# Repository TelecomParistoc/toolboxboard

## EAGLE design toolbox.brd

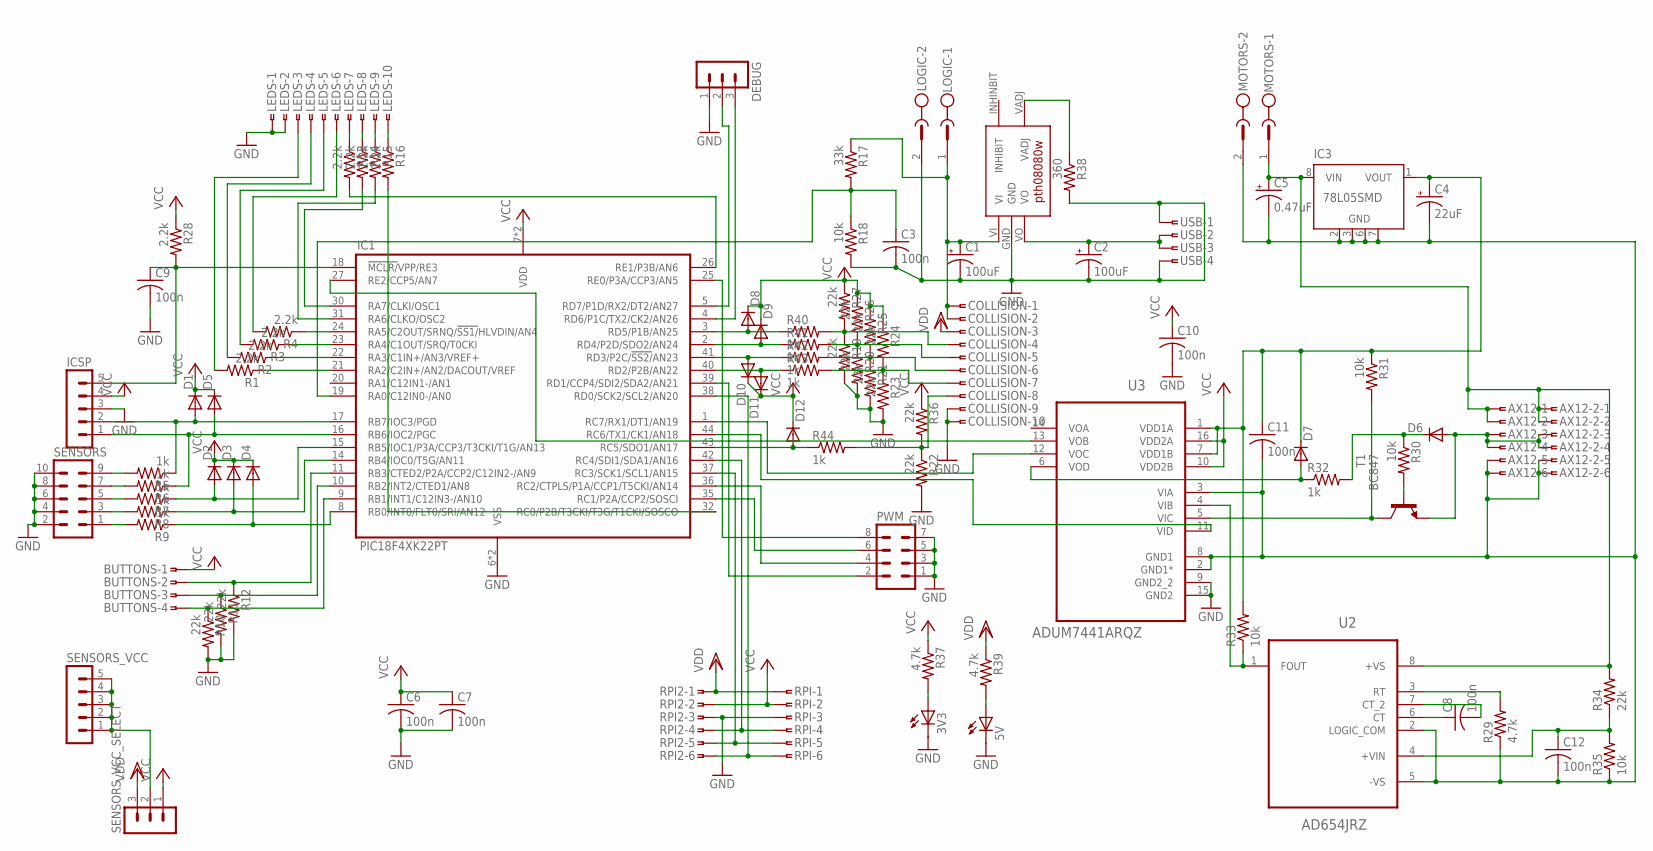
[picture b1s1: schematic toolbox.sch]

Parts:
3V3, 5V: LEDCHIPLED_0805; CHIPLED_0805
AX12, AX12-2: SMDTOP-6; SMDTOP6
BUTTONS: SMDTOP-4; SMDTOP4
C1, C2: 100uF; E2,5-6E
C3, C6, C7, C8, C9, C10, C11, C12: 100n; C0805
C4: 22uF; E2-5
C5: 0.47uF; E2-5
COLLISION: SMDTOP-10; SMDTOP10
D1, D2, D3, D4, D5, D6, D7, D8, D9, D10, D11, D12: DIODE-SOD523; SOD523
DEBUG: MA03-1
IC1: PIC18F4XK22PT; TQFP44
IC3: 78L05SMD; SO08
ICSP: MA05-1
LEDS: SMDTOP-10; SMDTOP10
LOGIC: MSTBV2
MOTORS: MSTBV2
PWM: MA04-2
R1, R2, R3, R4, R13, R14, R15, R16, R28: 2.2k; M0805
R5, R6, R7, R8, R9, R32, R40, R41, R42, R43, R44: 1k; M0805
R10, R11, R12, R19, R20, R21, R22, R23, R24, R25, R26, R27, R34, R36: 22k; M0805
R17: 33k; M0805
R18, R30, R31, R33, R35: 10k; M0805
R29, R37, R39: 4.7k; M0805
R38: 360; M0805
RPI, RPI2: SMDTOP-6; SMDTOP6
SENSORS: MA05-2
SENSORS_VCC: MA05-1
SENSORS_VCC_SELECT: MA03-1
T1: BC847; SOT23
U2: AD654JRZ; SOIC127P600X175-8N
U3: ADUM7441ARQZ; SOP64P600X175-16N
U$1: REGUL_PTH
USB: SMDTOP-4; SMDTOP4

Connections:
GND: 3V3.C, 5V.C, C1.-, C2.-, C3.2, C6.2, C7.2, C9.2, C10.2, COLLISION.9, COLLISION.10, DEBUG.1, IC1.6 (VSS), IC1.29 (VSS), ICSP.3, LEDS.1, LEDS.2, LOGIC.2, PWM.1, PWM.3, PWM.5, PWM.7, R10.2, R11.2, R12.2, R18.2, R19.2, R20.2, R21.2, R22.2, R23.2, R38.2, RPI.3, RPI2.3, SENSORS.2, SENSORS.4, SENSORS.6, SENSORS.8, SENSORS.10, U3.9 (GND2_2), U3.15 (GND2), U$1.GND, USB.1, USB.4
GND_MOTOR: AX12.5, AX12.6, AX12-2.5, AX12-2.6, C4.-, C5.-, C11.2, C12.2, IC3.2 (GND), IC3.3 (GND), IC3.6 (GND), IC3.7 (GND), MOTORS.2, R29.1, R35.1, U2.2 (LOGIC_COM), U2.5 (-VS), U3.2 (GND1*), U3.3 (VIA), U3.8 (GND1)
unnamed: D1.A, IC1.17 (RB7/IOC3/PGD), ICSP.2, R5.1
unnamed: D5.A, IC1.16 (RB6/IOC2/PGC), ICSP.1, R6.1
unnamed: C9.1, IC1.18 (!MCLR/!VPP/RE3), ICSP.5, R28.2
unnamed: LEDS.6, R4.2
unnamed: LEDS.5, R3.2
unnamed: LEDS.4, R2.2
unnamed: IC1.42 (RC4/SDI1/SDA1/AN16), RPI.4, RPI2.4
unnamed: IC1.37 (RC3/SCK1/SCL1/AN15), RPI.5, RPI2.5
unnamed: IC1.38 (RD0/SCK2/SCL2/AN20), RPI.6, RPI2.6
unnamed: LEDS.3, R1.2
unnamed: R5.2, SENSORS.9
unnamed: R6.2, SENSORS.7
unnamed: R7.2, SENSORS.5
unnamed: R8.2, SENSORS.3
unnamed: R9.2, SENSORS.1
unnamed: D2.A, IC1.15 (RB5/IOC1/P3A/CCP3/T3CKI/T1G/AN13), R7.1
unnamed: D3.A, IC1.14 (RB4/IOC0/T5G/AN11), R8.1
unnamed: D4.A, IC1.8 (RB0/INT0/FLT0/SRI/AN12), R9.1
unnamed: SENSORS_VCC.1, SENSORS_VCC.2, SENSORS_VCC.3, SENSORS_VCC.4, SENSORS_VCC.5, SENSORS_VCC_SELECT.2
unnamed: IC1.24 (RA5/C2OUT/SRNQ/!SS1/!HLVDIN/AN4), R4.1
unnamed: IC1.23 (RA4/C1OUT/SRQ/T0CKI), R3.1
unnamed: IC1.22 (RA3/C1IN+/AN3/VREF+), R2.1
unnamed: IC1.21 (RA2/C2IN+/AN2/DACOUT/VREF), R1.1
unnamed: BUTTONS.4, IC1.9 (RB1/INT1/C12IN3-/AN10), R10.1
unnamed: BUTTONS.2, IC1.11 (RB3/CTED2/P2A/CCP2/C12IN2-/AN9), R12.1
unnamed: BUTTONS.3, IC1.10 (RB2/INT2/CTED1/AN8), R11.1
unnamed: IC1.31 (RA6/CLKO/OSC2), R15.2
unnamed: IC1.30 (RA7/CLKI/OSC1), R14.2
unnamed: IC1.32 (RC0/P2B/T3CKI/T3G/T1CKI/SOSCO), R16.2
unnamed: IC1.26 (RE1/P3B/AN6), R13.2
unnamed: LEDS.10, R16.1
unnamed: LEDS.9, R15.1
unnamed: LEDS.8, R14.1
unnamed: LEDS.7, R13.1
unnamed: C1.+, COLLISION.1, COLLISION.2, LOGIC.1, R17.1, U$1.VI
unnamed: DEBUG.2, IC1.5 (RD7/P1D/RX2/DT2/AN27)
unnamed: C2.+, U$1.VO, USB.2, USB.3
unnamed: DEBUG.3, IC1.4 (RD6/P1C/TX2/CK2/AN26)
unnamed: C3.1, IC1.19 (RA0/C12IN0-/AN0), R17.2, R18.1
unnamed: IC1.35 (RC1/P2A/CCP2/SOSCI), PWM.6
unnamed: COLLISION.4, R19.1, R27.2, R40.2
unnamed: COLLISION.5, R20.1, R26.2, R41.2
unnamed: COLLISION.6, R21.1, R25.2, R42.2
unnamed: COLLISION.7, R23.1, R24.2, R43.2
unnamed: COLLISION.8, R22.1, R36.2, R44.2
unnamed: IC1.36 (RC2/CTPLS/P1A/CCP1/T5CKI/AN14), PWM.4
unnamed: IC1.25 (RE0/P3A/CCP3/AN5), PWM.8
unnamed: IC1.39 (RD1/CCP4/SDI2/SDA2/AN21), PWM.2
unnamed: C12.1, R34.1, R35.2, U2.4 (+VIN)
unnamed: C8.1, U2.6 (CT)
unnamed: R30.2, T1.1 (B)
unnamed: AX12.3, AX12.4, AX12-2.3, AX12-2.4, D6.A, T1.2 (E)
unnamed: D6.C, R30.1, R32.2
unnamed: IC1.1 (RC7/RX1/DT1/AN19), U3.12 (VOC)
unnamed: R31.2, T1.3 (C), U3.5 (VIC)
unnamed: IC1.44 (RC6/TX1/CK1/AN18), U3.11 (VID)
unnamed: IC1.27 (RE2/CCP5/AN7), U3.13 (VOB)
unnamed: R38.1, U$1.VADJ
unnamed: D7.A, R32.1, U3.6 (VOD)
unnamed: 3V3.A, R37.2
unnamed: AX12.1, AX12.2, AX12-2.1, AX12-2.2, C5.+, IC3.8 (VIN), MOTORS.1, R34.2, U2.8 (+VS)
unnamed: C8.2, U2.7 (CT_2)
unnamed: R33.1, U2.1 (FOUT), U3.4 (VIB)
unnamed: 5V.A, R39.2
unnamed: R29.2, U2.3 (RT)
unnamed: D12.A, IC1.43 (RC5/SDO1/AN17), R44.1
unnamed: D8.A, IC1.3 (RD5/P1B/AN25), R40.1
unnamed: C4.+, C11.1, D7.C, IC3.1 (VOUT), R31.1, R33.2, U3.1 (VDD1A), U3.7 (VDD1B)
unnamed: D9.A, IC1.2 (RD4/P2D/SDO2/AN24), R41.1
unnamed: D10.A, IC1.41 (RD3/P2C/!SS2/!AN23), R42.1
unnamed: D11.A, IC1.40 (RD2/P2B/AN22), R43.1
VCC: BUTTONS.1, C6.1, C7.1, C10.1, D1.C, D2.C, D3.C, D4.C, D5.C, D8.C, D9.C, D10.C, D11.C, D12.C, IC1.7 (VDD), IC1.28 (VDD), ICSP.4, R24.1, R25.1, R26.1, R27.1, R28.1, R36.1, R37.1, RPI.2, RPI2.2, SENSORS_VCC_SELECT.1, U3.10 (VDD2B), U3.16 (VDD2A)
VDD: COLLISION.3, R39.1, RPI.1, RPI2.1, SENSORS_VCC_SELECT.3

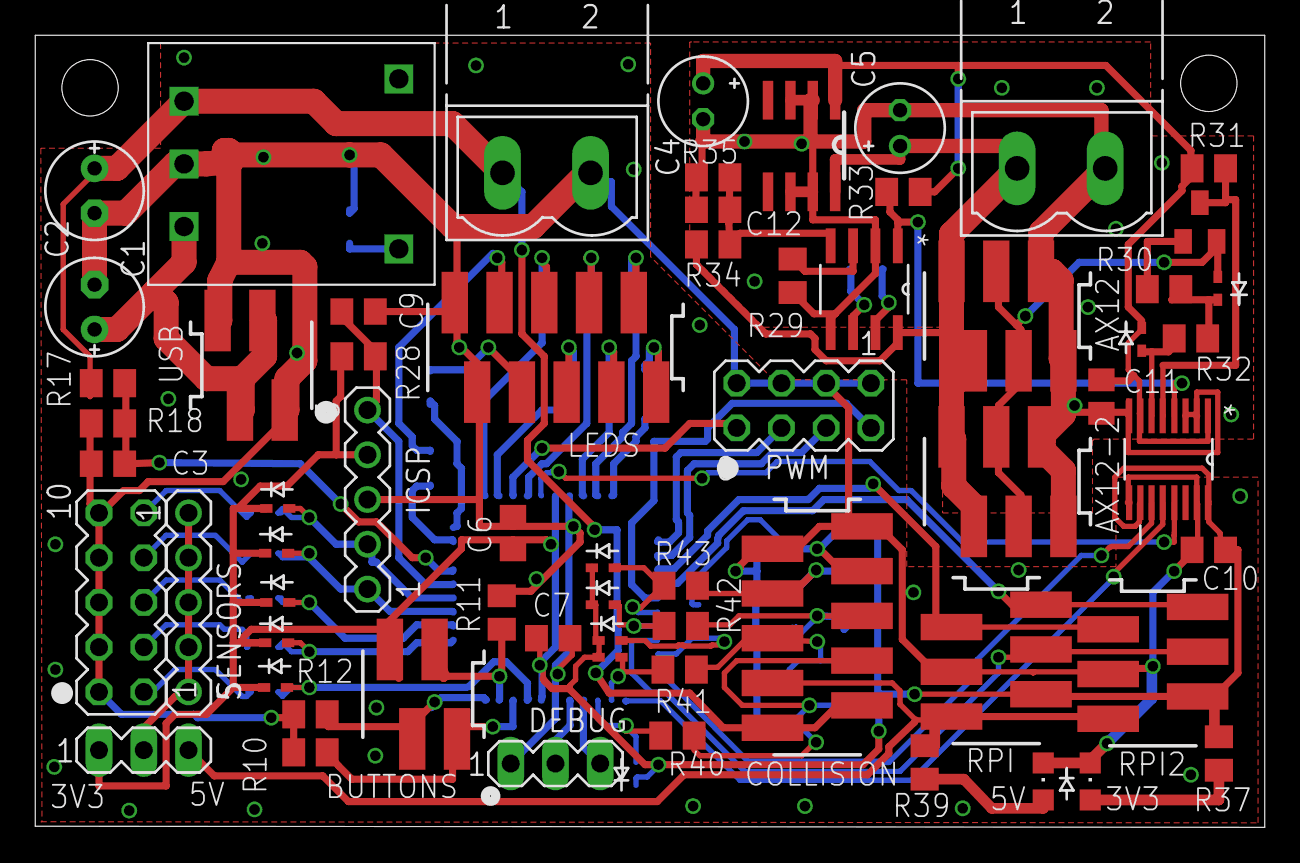
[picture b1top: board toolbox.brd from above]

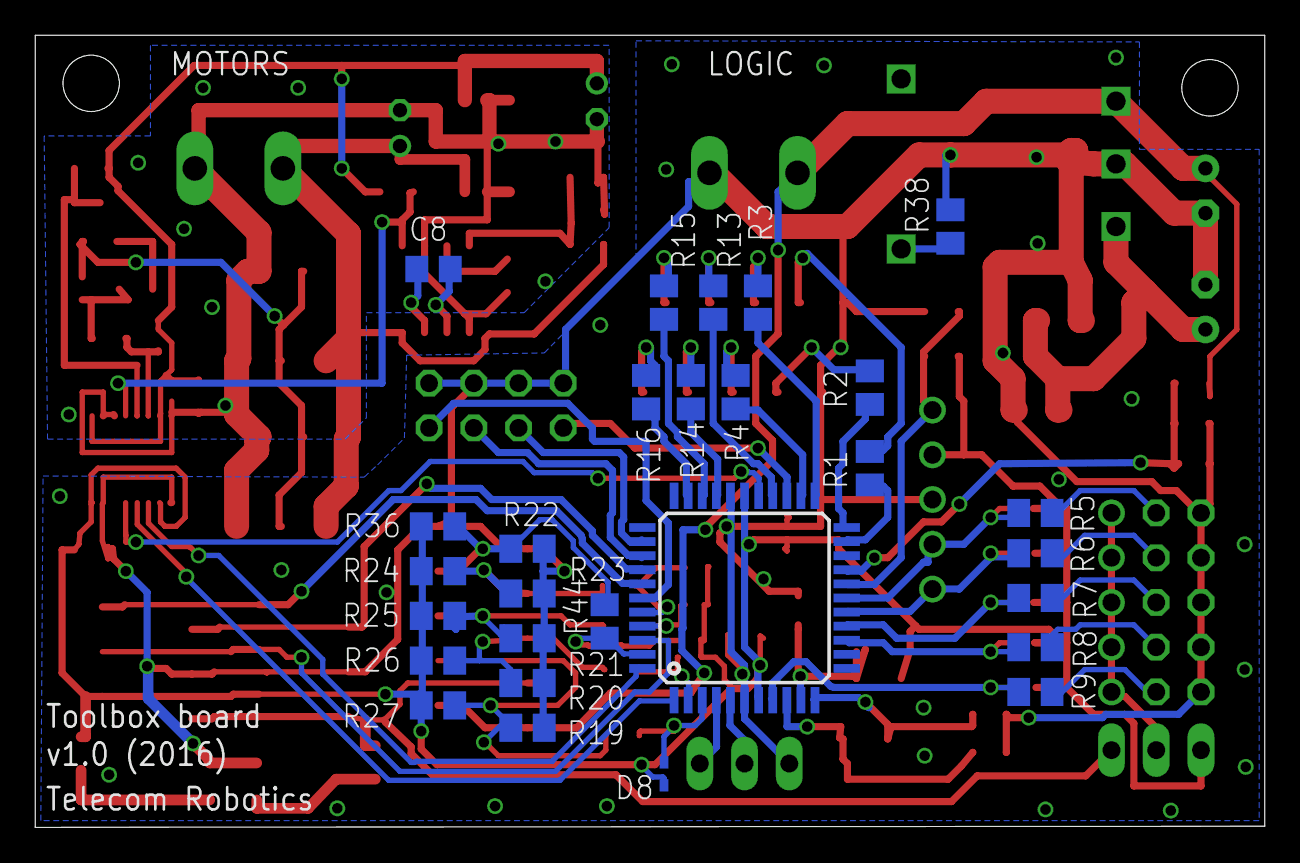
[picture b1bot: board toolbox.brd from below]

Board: 2 copper layers, 69.8 x 45.0 mm, 92 parts (28 on the bottom side), 75 nets.

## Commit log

2015-12-31 initial commit includes used librairies and datasheets
2015-12-31 added board
2016-01-10 added gitignore and design rules
2016-01-10 WIP replaced AX-12 connector with 2x6pin micromatch routed motor side parts, sensor, buttons and LEDs connectors
2016-01-12 WIP finished routing the board Removed useless datasheet
2016-01-12 moved labels and created ground planes with vias between them
2016-01-15 moved LED name
2016-01-15 added diode symbols on PCB
2016-01-15 enlarged diode symbols
2016-01-16 added clipping circuit for collision sensors
2016-01-16 improved silk screen
2016-01-16 circuit checked, added filtering capacitor and fixed a last clearance error
2016-01-19 added connector doc
